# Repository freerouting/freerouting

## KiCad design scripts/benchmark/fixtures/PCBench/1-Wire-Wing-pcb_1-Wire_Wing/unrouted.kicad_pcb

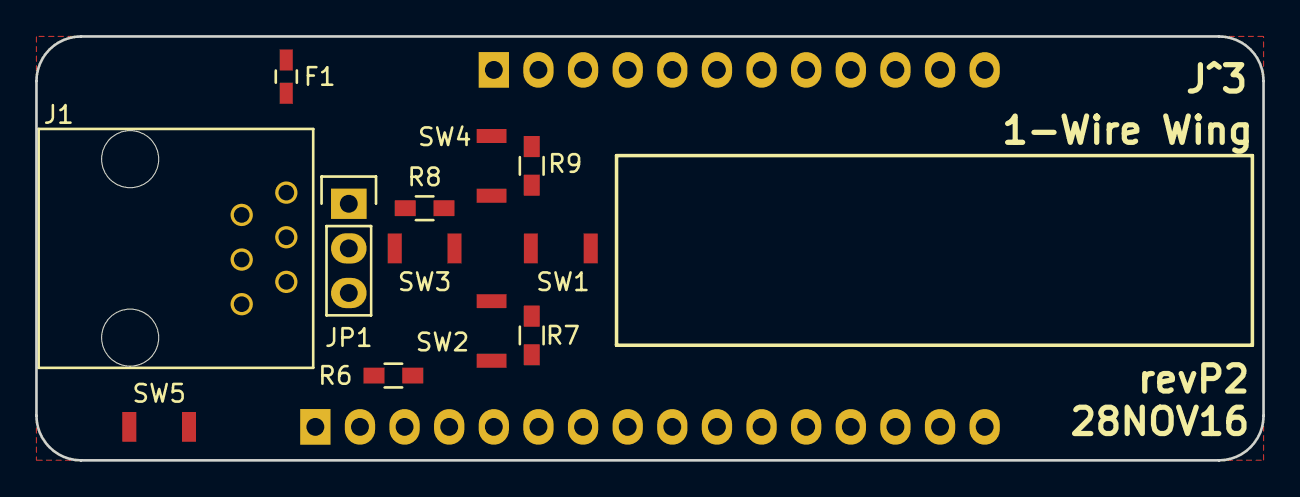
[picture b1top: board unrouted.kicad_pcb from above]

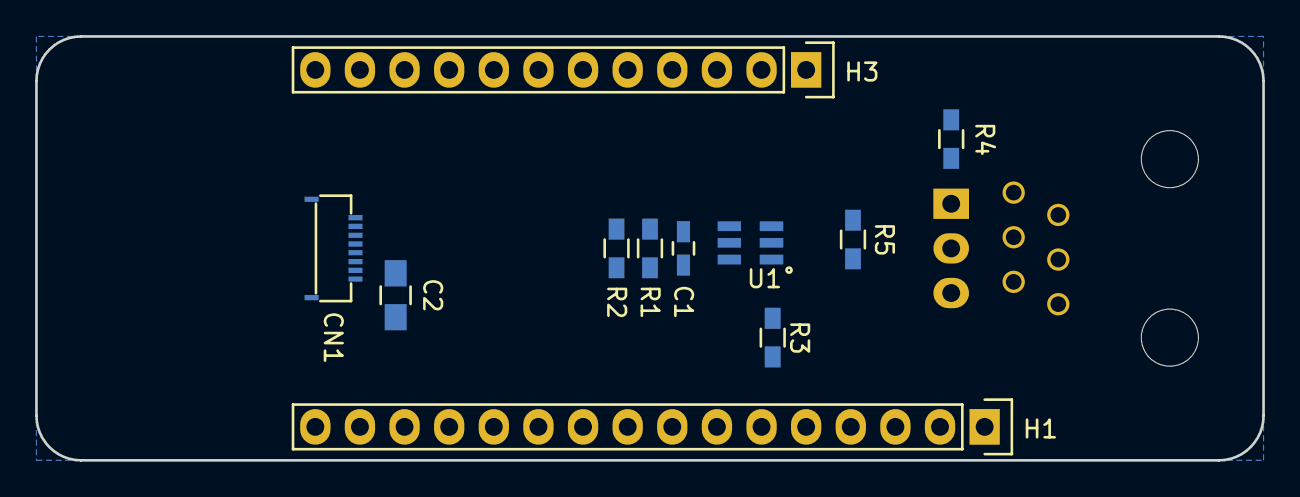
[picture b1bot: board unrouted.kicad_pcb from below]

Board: 2 copper layers, 69.9 x 24.1 mm, 23 parts (11 on the bottom side), 20 nets, no tracks yet.

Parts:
C1: 0.1uF; C_0603_HandSoldering
C2: 2uF; C_0805_HandSoldering
CN1: CONN_01X08; HIROSE_FH19C-8S-0.5SH(05)
F1: FUSE; C_0603_HandSoldering
H1: CONN_01X16; Pin_Header_Straight_1x16
H3: CONN_01X12; Pin_Header_Straight_1x12
J1: RJ11; TE_6P6C_5555165-1
JP1: CONN_01X03; Pin_Header_Straight_1x03
R1, R2, R7: 3.3K; R_0603_HandSoldering
R3: 2.2K; R_0603_HandSoldering
R4: 1K; R_0603_HandSoldering
R5: DNI; R_0603_HandSoldering
R6, R8: 10K; R_0603_HandSoldering
R9: 33K; R_0603_HandSoldering
SW1, SW2, SW3, SW4, SW5: SW_PUSH_SMALL_H; OMRON_B3U-1000P
U1: DS2484R+; SOT95P280X125-6N

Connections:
+3V3: C1.1, C2.1, CN1.6, F1.1, H1.2, R1.1, R2.1, R3.1, R4.1, R6.1, U1.6
/1-Wire: J1.3, JP1.2
/CS: CN1.3, H3.6
/DISP: CN1.5, H3.8
/EXTCOMIN: CN1.4, H3.7
/MOSI: CN1.2, H1.12
/OWM: H3.4, JP1.1, R4.2
/SCL: H3.11, R1.2, U1.3
/SCLK: CN1.1, H1.11
/SDA: H3.12, R2.2, U1.2
/~RESET: H1.1, SW5.1
/~SLPZ: H3.5, R5.2
GND: C1.2, C2.2, CN1.8, H1.4, H1.16, J1.2, J1.4, R7.2, R8.2, R9.2, SW1.1, SW5.2, U1.4
unnamed: F1.2, J1.1
unnamed: H1.6, R6.2, SW1.2, SW2.2, SW3.2, SW4.2
unnamed: JP1.3, U1.5
unnamed: R3.2, R5.1, U1.1
unnamed: R7.1, SW2.1
unnamed: R8.1, SW3.1
unnamed: R9.1, SW4.1

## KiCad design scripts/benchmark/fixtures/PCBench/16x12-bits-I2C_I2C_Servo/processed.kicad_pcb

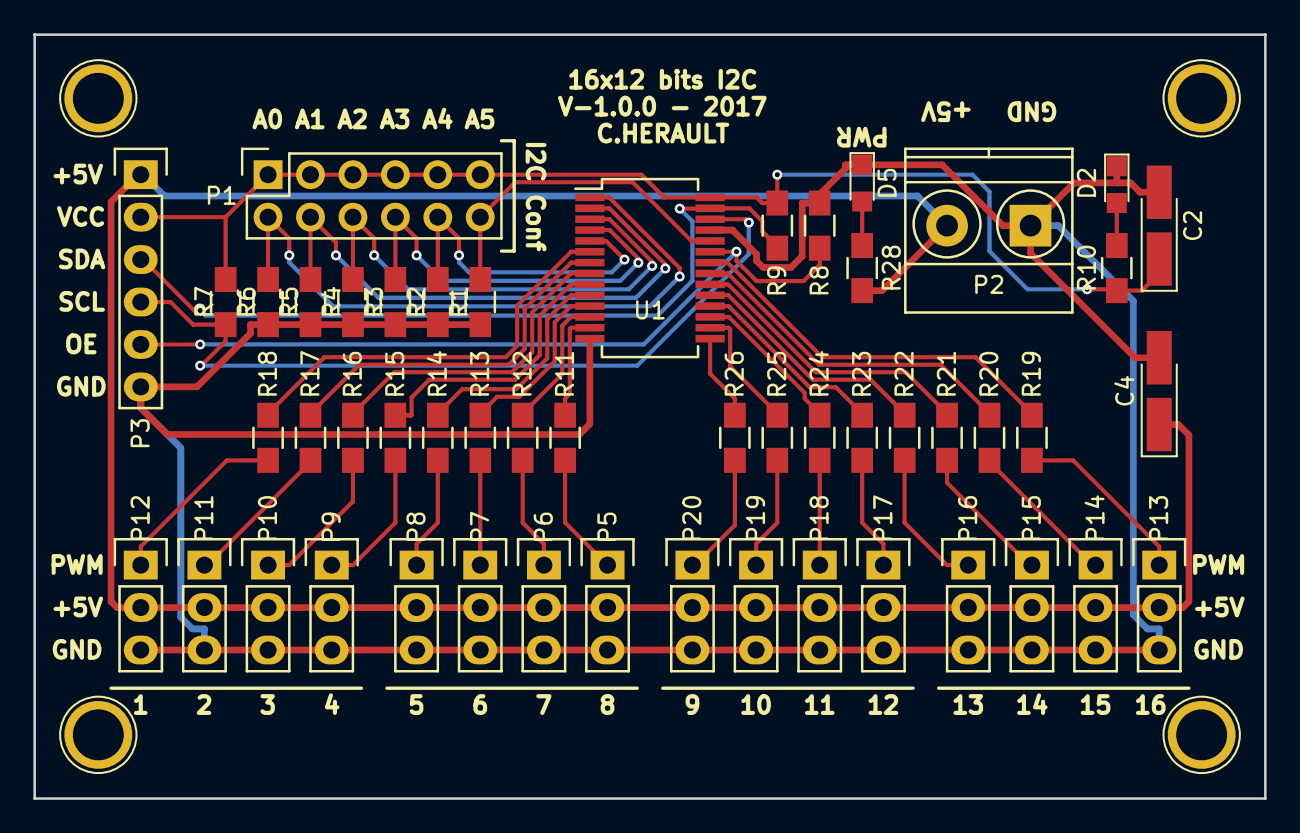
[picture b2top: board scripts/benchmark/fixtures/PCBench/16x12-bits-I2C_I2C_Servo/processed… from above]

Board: 2 copper layers, 73.7 x 45.7 mm, 51 parts (0 on the bottom side), 46 nets.

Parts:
C2, C4: 10uF; CP_Tantalum_Case-S_EIA-3216-12_Hand
D2, D5: LED_Small; LED_0805
P1: CONN_02X06; Socket_Strip_Straight_2x06
P2: CONN_01X02; TerminalBlock_Pheonix_MKDS1.5-2pol
P3: CONN_01X06; Socket_Strip_Straight_1x06
P5, P6, P7, P8, P9, P10, P11, P12, P13, P14, P15, P16, P17, P18, P19, P20: CONN_01X03; Socket_Strip_Straight_1x03
R1, R2, R3, R4, R5, R6, R7, R8, R9: 10K; R_0805_HandSoldering
R10, R28: 470; R_0805_HandSoldering
R11, R12, R13, R14, R15, R16, R17, R18, R19, R20, R21, R22, R23, R24, R25, R26: 220; R_0805_HandSoldering
U1: PCA9685; SSOP-28_5.3x10.2mm_Pitch0.65mm

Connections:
+5V: C4.1, P2.2, P3.1, P5.2, P6.2, P7.2, P8.2, P9.2, P10.2, P11.2, P12.2, P13.2, P14.2, P15.2, P16.2, P17.2, P18.2, P19.2, P20.2, R28.2
GND: C2.2, C4.2, D2.1, D5.1, P2.1, P3.6, P5.3, P6.3, P7.3, P8.3, P9.3, P10.3, P11.3, P12.3, P13.3, P14.3, P15.3, P16.3, P17.3, P18.3, P19.3, P20.3, R1.2, R2.2, R3.2, R4.2, R5.2, R6.2, R8.2, U1.14, U1.25
unnamed: D2.2, R10.1
unnamed: D5.2, R28.1
unnamed: P1.2, R6.1, U1.1
unnamed: P1.4, R5.1, U1.2
unnamed: P1.6, R4.1, U1.3
unnamed: P1.8, R3.1, U1.4
unnamed: P1.10, R2.1, U1.5
unnamed: P1.12, R1.1, U1.24
unnamed: P5.1, R11.1
unnamed: P6.1, R12.1
unnamed: P7.1, R13.1
unnamed: P8.1, R14.1
unnamed: P9.1, R15.1
unnamed: P10.1, R16.1
unnamed: P11.1, R17.1
unnamed: P12.1, R18.1
unnamed: P13.1, R19.1
unnamed: P14.1, R20.1
unnamed: P15.1, R21.1
unnamed: P16.1, R22.1
unnamed: P17.1, R23.1
unnamed: P18.1, R24.1
unnamed: P19.1, R25.1
unnamed: P20.1, R26.1
OE: P3.5, R8.1, U1.23
PWM0: R18.2, U1.6
PWM1: R17.2, U1.7
PWM2: R16.2, U1.8
PWM3: R15.2, U1.9
PWM4: R14.2, U1.10
PWM5: R13.2, U1.11
PWM6: R12.2, U1.12
PWM7: R11.2, U1.13
PWM8: R26.2, U1.15
PWM9: R25.2, U1.16
PWM10: R24.2, U1.17
PWM11: R23.2, U1.18
PWM12: R22.2, U1.19
PWM13: R21.2, U1.20
PWM14: R20.2, U1.21
PWM15: R19.2, U1.22
SCL: P3.4, R7.2, U1.26
SDA: P3.3, R9.2, U1.27
VCC: C2.1, P1.1, P1.3, P1.5, P1.7, P1.9, P1.11, P3.2, R7.1, R9.1, R10.2, U1.28

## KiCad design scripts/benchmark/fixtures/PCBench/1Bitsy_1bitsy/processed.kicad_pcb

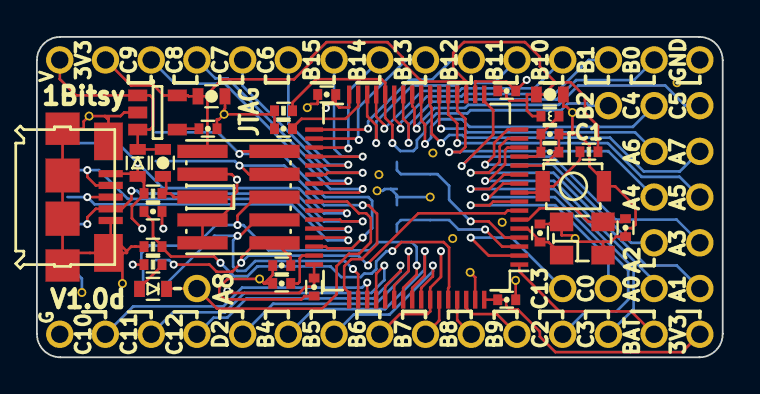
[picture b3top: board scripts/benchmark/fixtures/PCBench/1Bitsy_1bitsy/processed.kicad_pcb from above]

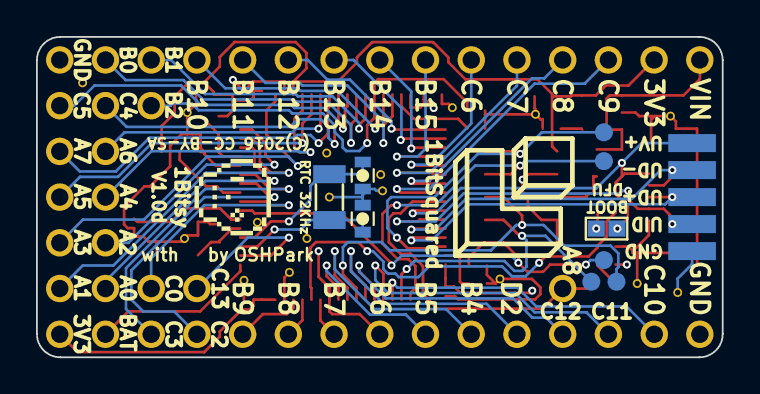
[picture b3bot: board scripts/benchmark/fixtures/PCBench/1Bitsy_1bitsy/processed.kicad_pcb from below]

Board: 4 copper layers, 38.1 x 17.8 mm, 88 parts (14 on the bottom side), 63 nets.

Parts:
C1, C5, C13: 4u7; C_0603
C2, C15: 1u; C_0402
C3: 470p; C_0402
C4, C10, C11, C12, C14, C18: 100n; C_0402
C6, C7: 10p; C_0603
C8, C9: 10p; C_0402
C16, C17: 2u2; C_0402
D1: >100mA; D_0603
J1: BOOT; J_0603
L1: 600 Ferrite; L_0402
LED1: ORA; D_0603
P1, P2, P3, P4, P5, P6, P7, P8, P9, P10, P11, P12, P13, P14, P15, P16, P17, P18, P19, P20, P21, P22, P23, P25, P26, P27, P28, P29, P30, P31, P32, P33, P34, P35, P36, P37, P38, P39, P40, P41, P42, P53, P54, P55: CONN_01X01; Pin_Header_Straight_Round_1x01
P24: USB_OTG; Connector_USB_Micro_B_SMD
P43, P44, P45, P46, P47: TP; POGO_PAD_SMD_R_1x1
P48, P49, P50, P51, P52: CONN_01X01; PAD_SMD_1x2.65
R1, R2, R3, R5: 10k; R_0402
R4: 300; R_0402
SW1: TACT; Tact_Switch_Top_B3U-1000P
U1: VREG_3V3; SOT-23-5
U2: STM32F415RGT; LQFP-64_10x10mm_Pitch0.5mm
X1: 32.768kHz; ABS07
X2: 25MHz; ABM8
X3: JTAG-10; FTSH-105-XX-X-DV

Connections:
+3V3: C5.1, C10.1, C11.1, C12.1, C13.1, C14.1, L1.1, P42.1, P54.1, R4.1, R5.1, U1.5, U2.19, U2.32, U2.48, U2.64, X3.1
/BOOT0: C15.2, R3.1, U2.60
/BUTTON: R5.2, SW1.2, U2.9
/JTAG_RST: C18.1, P47.1, U2.7, X3.10
/JTAG_TCK: P44.1, U2.49, X3.4
/JTAG_TDI: P46.1, U2.50, X3.8
/JTAG_TDO: P45.1, U2.55, X3.6
/JTAG_TMS: P43.1, U2.46, X3.2
/OSC32_IN: C6.2, U2.3, X1.2
/OSC32_OUT: C7.2, U2.4, X1.1
/OSC_IN: C8.2, U2.5, X2.1
/OSC_OUT: C9.2, U2.6, X2.2
/PA0: P1.1, U2.14
/PA1: P2.1, U2.15
/PA2: P3.1, U2.16
/PA3: P4.1, U2.17
/PA4: P5.1, U2.20
/PA5: P6.1, U2.21
/PA6: P7.1, U2.22
/PA7: P8.1, U2.23
/PA8: LED1.C, P9.1, U2.41
/PB0: P25.1, U2.26
/PB1: P26.1, U2.27
/PB2: P27.1, R2.1, U2.28
/PB4: P28.1, U2.56
/PB5: P29.1, U2.57
/PB6: P30.1, U2.58
/PB7: P31.1, U2.59
/PB8: P32.1, U2.61
/PB9: P33.1, U2.62
/PB10: P34.1, U2.29
/PB11: P35.1, U2.30
/PB12: P36.1, U2.33
/PB13: P37.1, U2.34
/PB14: P38.1, U2.35
/PB15: P39.1, U2.36
/PC0: P10.1, U2.8
/PC2: P12.1, U2.10
/PC3: P13.1, U2.11
/PC4: P14.1, U2.24
/PC5: P15.1, U2.25
/PC6: P16.1, U2.37
/PC7: P17.1, U2.38
/PC8: P18.1, U2.39
/PC9: P19.1, U2.40
/PC10: P20.1, U2.51
/PC11: P21.1, U2.52
/PC12: P22.1, U2.53
/PC13: P23.1, U2.2
/PD2: P11.1, U2.54
/USB_D+: P24.3, P50.1, U2.45
/USB_D-: P24.2, P49.1, U2.44
/USB_ID: P24.4, P51.1, U2.43
/USB_VBUS: D1.A, J1.1, P24.1, P48.1, R1.1, U2.42
/VBAT: P53.1, U2.1
/VIN: C1.1, D1.C, P40.1, U1.1, U1.3
GND: C1.2, C2.2, C3.2, C4.2, C5.2, C6.1, C7.1, C8.1, C9.1, C10.2, C11.2, C12.2, C13.2, C14.2, C16.2, C17.2, C18.2, P24.5, P24.GND, P41.1, P52.1, P55.1, R1.2, R2.2, R3.2, SW1.1, U1.2, U2.12, U2.18, U2.63, X2.GND, X3.3, X3.5, X3.7, X3.9
unnamed: C2.1, C4.1, L1.2, U2.13
unnamed: C3.1, U1.4
unnamed: C15.1, J1.2
unnamed: C16.1, U2.47
unnamed: C17.1, U2.31
unnamed: LED1.A, R4.2

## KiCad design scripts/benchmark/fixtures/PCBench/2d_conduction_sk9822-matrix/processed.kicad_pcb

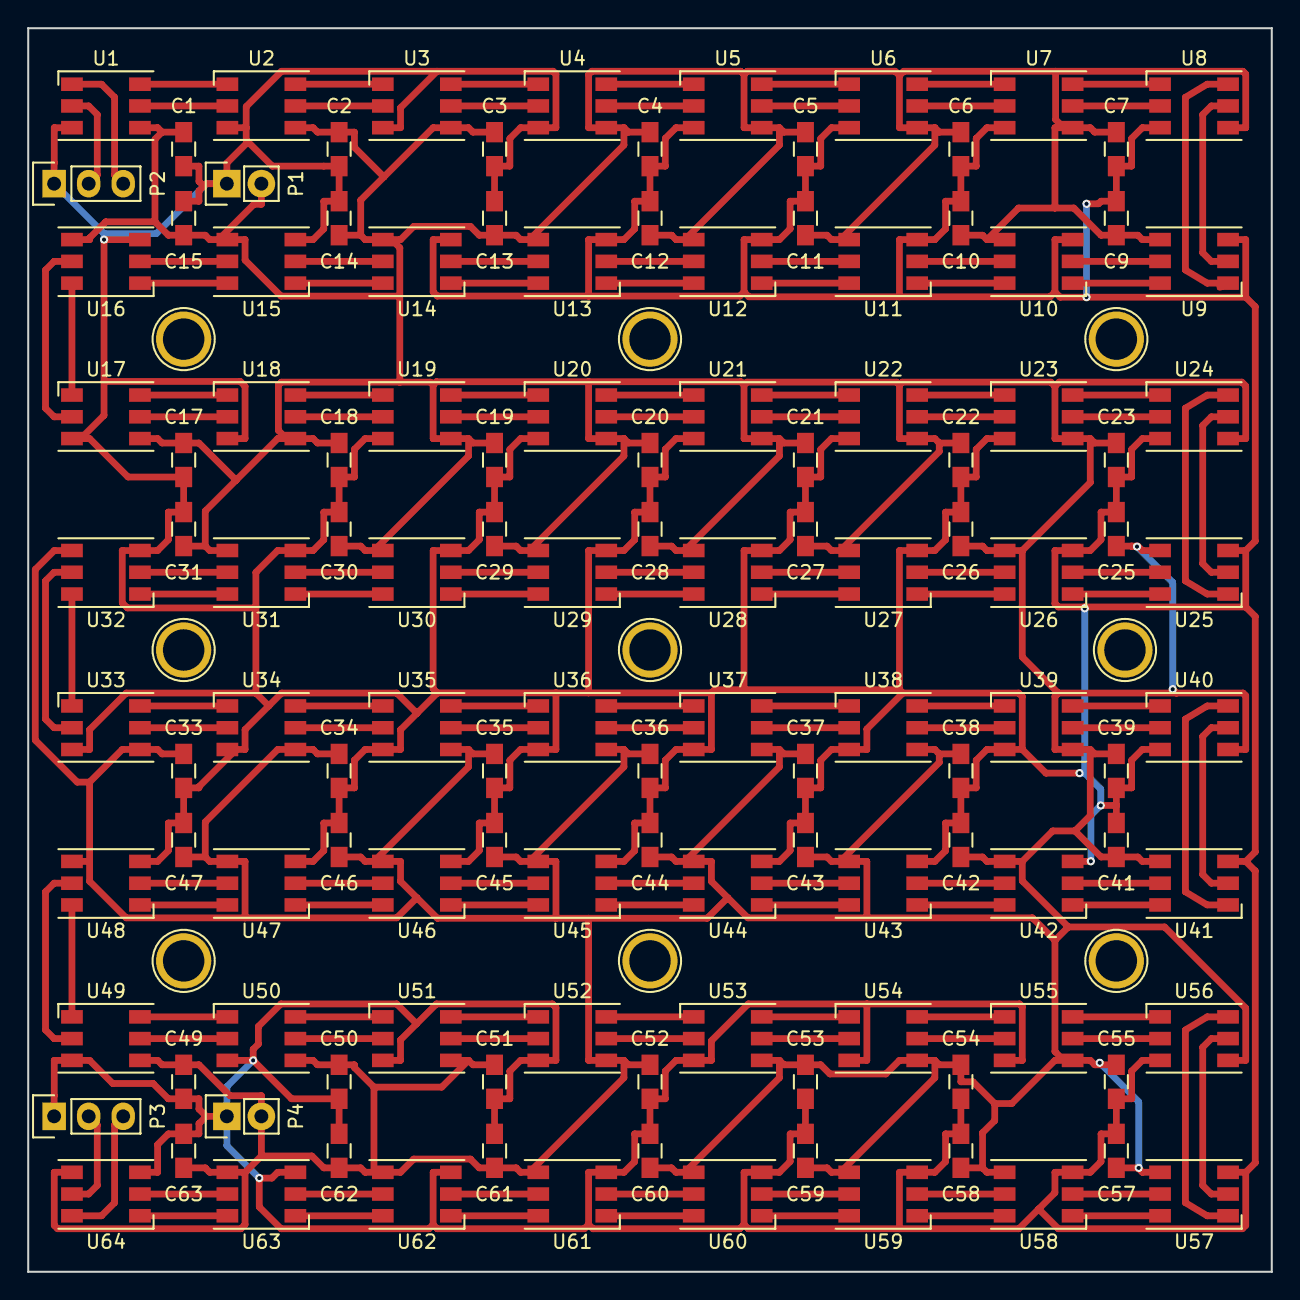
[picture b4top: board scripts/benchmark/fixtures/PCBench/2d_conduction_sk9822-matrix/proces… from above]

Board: 2 copper layers, 91.4 x 91.4 mm, 133 parts (0 on the bottom side), 132 nets.

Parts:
C1, C2, C3, C4, C5, C6, C7, C9, C10, C11, C12, C13, C14, C15, C17, C18, C19, C20, C21, C22, C23, C25, C26, C27, C28, C29, C30, C31, C33, C34, C35, C36, C37, C38, C39, C41, C42, C43, C44, C45, C46, C47, C49, C50, C51, C52, C53, C54, C55, C57, C58, C59, C60, C61, C62, C63: 0.1uF; C_0805_HandSoldering
H1, H2, H3, H4, H5, H6, H7, H8, H9: 1pin
P1: PWR IN; Pin_Header_Straight_1x02
P2: DATA IN; Pin_Header_Straight_1x03
P3: DATA OUT; Pin_Header_Straight_1x03
P4: PWR OUT; Pin_Header_Straight_1x02
U1, U2, U3, U4, U5, U6, U7, U8, U9, U10, U11, U12, U13, U14, U15, U16, U17, U18, U19, U20, U21, U22, U23, U24, U25, U26, U27, U28, U29, U30, U31, U32, U33, U34, U35, U36, U37, U38, U39, U40, U41, U42, U43, U44, U45, U46, U47, U48, U49, U50, U51, U52, U53, U54, U55, U56, U57, U58, U59, U60, U61, U62, U63, U64: SK9822; LED_WS2812-PLCC6

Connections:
+5V: C1.2, C2.2, C3.2, C4.2, C5.2, C6.2, C7.2, C9.2, C10.2, C11.2, C12.2, C13.2, C14.2, C15.2, C17.2, C18.2, C19.2, C20.2, C21.2, C22.2, C23.2, C25.2, C26.2, C27.2, C28.2, C29.2, C30.2, C31.2, C33.2, C34.2, C35.2, C36.2, C37.2, C38.2, C39.2, C41.2, C42.2, C43.2, C44.2, C45.2, C46.2, C47.2, C49.2, C50.2, C51.2, C52.2, C53.2, C54.2, C55.2, C57.2, C58.2, C59.2, C60.2, C61.2, C62.2, C63.2, P1.2, P4.2, U1.4, U2.4, U3.4, U4.4, U5.4, U6.4, U7.4, U8.4, U9.4, U10.4, U11.4, U12.4, U13.4, U14.4, U15.4, U16.4, U17.4, U18.4, U19.4, U20.4, U21.4, U22.4, U23.4, U24.4, U25.4, U26.4, U27.4, U28.4, U29.4, U30.4, U31.4, U32.4, U33.4, U34.4, U35.4, U36.4, U37.4, U38.4, U39.4, U40.4, U41.4, U42.4, U43.4, U44.4, U45.4, U46.4, U47.4, U48.4, U49.4, U50.4, U51.4, U52.4, U53.4, U54.4, U55.4, U56.4, U57.4, U58.4, U59.4, U60.4, U61.4, U62.4, U63.4, U64.4
/CKI: P2.2, U1.2
/CKO: P3.2, U64.5
/CKO8: U8.5, U9.2
/CKO16: U16.5, U17.2
/CKO24: U24.5, U25.2
/CKO32: U32.5, U33.2
/CKO40: U40.5, U41.2
/CKO48: U48.5, U49.2
/CKO56: U56.5, U57.2
/SDI: P2.3, U1.1
/SDO: P3.3, U64.6
/SDO8: U8.6, U9.1
/SDO16: U16.6, U17.1
/SDO24: U24.6, U25.1
/SDO32: U32.6, U33.1
/SDO40: U40.6, U41.1
/SDO48: U48.6, U49.1
/SDO56: U56.6, U57.1
GND: C1.1, C2.1, C3.1, C4.1, C5.1, C6.1, C7.1, C9.1, C10.1, C11.1, C12.1, C13.1, C14.1, C15.1, C17.1, C18.1, C19.1, C20.1, C21.1, C22.1, C23.1, C25.1, C26.1, C27.1, C28.1, C29.1, C30.1, C31.1, C33.1, C34.1, C35.1, C36.1, C37.1, C38.1, C39.1, C41.1, C42.1, C43.1, C44.1, C45.1, C46.1, C47.1, C49.1, C50.1, C51.1, C52.1, C53.1, C54.1, C55.1, C57.1, C58.1, C59.1, C60.1, C61.1, C62.1, C63.1, P1.1, P2.1, P3.1, P4.1, U1.3, U2.3, U3.3, U4.3, U5.3, U6.3, U7.3, U8.3, U9.3, U10.3, U11.3, U12.3, U13.3, U14.3, U15.3, U16.3, U17.3, U18.3, U19.3, U20.3, U21.3, U22.3, U23.3, U24.3, U25.3, U26.3, U27.3, U28.3, U29.3, U30.3, U31.3, U32.3, U33.3, U34.3, U35.3, U36.3, U37.3, U38.3, U39.3, U40.3, U41.3, U42.3, U43.3, U44.3, U45.3, U46.3, U47.3, U48.3, U49.3, U50.3, U51.3, U52.3, U53.3, U54.3, U55.3, U56.3, U57.3, U58.3, U59.3, U60.3, U61.3, U62.3, U63.3, U64.3
unnamed: U1.5, U2.2
unnamed: U1.6, U2.1
unnamed: U2.5, U3.2
unnamed: U2.6, U3.1
unnamed: U3.5, U4.2
unnamed: U3.6, U4.1
unnamed: U4.5, U5.2
unnamed: U4.6, U5.1
unnamed: U5.5, U6.2
unnamed: U5.6, U6.1
unnamed: U6.5, U7.2
unnamed: U6.6, U7.1
unnamed: U7.5, U8.2
unnamed: U7.6, U8.1
unnamed: U9.6, U10.1
unnamed: U9.5, U10.2
unnamed: U10.5, U11.2
unnamed: U10.6, U11.1
unnamed: U11.5, U12.2
unnamed: U11.6, U12.1
unnamed: U12.5, U13.2
unnamed: U12.6, U13.1
unnamed: U13.5, U14.2
unnamed: U13.6, U14.1
unnamed: U14.5, U15.2
unnamed: U14.6, U15.1
unnamed: U15.5, U16.2
unnamed: U15.6, U16.1
unnamed: U17.5, U18.2
unnamed: U17.6, U18.1
unnamed: U18.5, U19.2
unnamed: U18.6, U19.1
unnamed: U19.5, U20.2
unnamed: U19.6, U20.1
unnamed: U20.5, U21.2
unnamed: U20.6, U21.1
unnamed: U21.5, U22.2
unnamed: U21.6, U22.1
unnamed: U22.5, U23.2
unnamed: U22.6, U23.1
unnamed: U23.5, U24.2
unnamed: U23.6, U24.1
unnamed: U25.5, U26.2
unnamed: U25.6, U26.1
unnamed: U26.5, U27.2
unnamed: U26.6, U27.1
unnamed: U27.5, U28.2
unnamed: U27.6, U28.1
unnamed: U28.5, U29.2
unnamed: U28.6, U29.1
unnamed: U29.5, U30.2
unnamed: U29.6, U30.1
unnamed: U30.5, U31.2
unnamed: U30.6, U31.1
unnamed: U31.5, U32.2
unnamed: U31.6, U32.1
unnamed: U33.5, U34.2
unnamed: U33.6, U34.1
unnamed: U34.5, U35.2
unnamed: U34.6, U35.1
unnamed: U35.5, U36.2
unnamed: U35.6, U36.1
unnamed: U36.5, U37.2
unnamed: U36.6, U37.1
unnamed: U37.5, U38.2
unnamed: U37.6, U38.1
unnamed: U38.5, U39.2
unnamed: U38.6, U39.1
unnamed: U39.5, U40.2
unnamed: U39.6, U40.1
unnamed: U41.5, U42.2
unnamed: U41.6, U42.1
unnamed: U42.5, U43.2
unnamed: U42.6, U43.1
unnamed: U43.5, U44.2
unnamed: U43.6, U44.1
unnamed: U44.5, U45.2
unnamed: U44.6, U45.1
unnamed: U45.5, U46.2
unnamed: U45.6, U46.1
unnamed: U46.5, U47.2
unnamed: U46.6, U47.1
unnamed: U47.5, U48.2
unnamed: U47.6, U48.1
unnamed: U49.5, U50.2
unnamed: U49.6, U50.1
unnamed: U50.5, U51.2
unnamed: U50.6, U51.1
unnamed: U51.5, U52.2
unnamed: U51.6, U52.1
unnamed: U52.5, U53.2
unnamed: U52.6, U53.1
unnamed: U53.5, U54.2
unnamed: U53.6, U54.1
unnamed: U54.5, U55.2
unnamed: U54.6, U55.1
unnamed: U55.5, U56.2
unnamed: U55.6, U56.1
unnamed: U57.5, U58.2
unnamed: U57.6, U58.1
unnamed: U58.5, U59.2
unnamed: U58.6, U59.1
unnamed: U59.5, U60.2
unnamed: U59.6, U60.1
unnamed: U60.5, U61.2
unnamed: U60.6, U61.1
unnamed: U61.5, U62.2
unnamed: U61.6, U62.1
unnamed: U62.5, U63.2
unnamed: U62.6, U63.1
unnamed: U63.5, U64.2
unnamed: U63.6, U64.1

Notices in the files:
scripts/benchmark/fixtures/PCBench/1Bitsy_1bitsy/processed.kicad_pcb:
(C) 2016 Piotr Esden-Tempski
(C) 2016 1BitSquared LLC
License: CC-BY-SA V4.0
(C)2016 CC-BY-SA
